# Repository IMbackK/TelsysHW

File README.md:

# Telsys Hardware

Telsys is a small integrated wireless bluetooth low energy measurement amplifier and digitizer. Its primary intention is the use with strain gauges in sensor integrated structures. Sutch as the strain reporting pipe seen below. The firmware for the nrf52 used in this design can be found here: https://github.com/IMbackK/TelsysFW. A GUI client for reciveing the data as well as to examine the data can be found here: https://github.com/IMbackK/TelsysMaster

These are kicad files detailing the shematic and board design of the Telsys device.
Kicad can be found here: https://www.kicad.org/

License: gpl-3.0 only, see license/GPL.txt

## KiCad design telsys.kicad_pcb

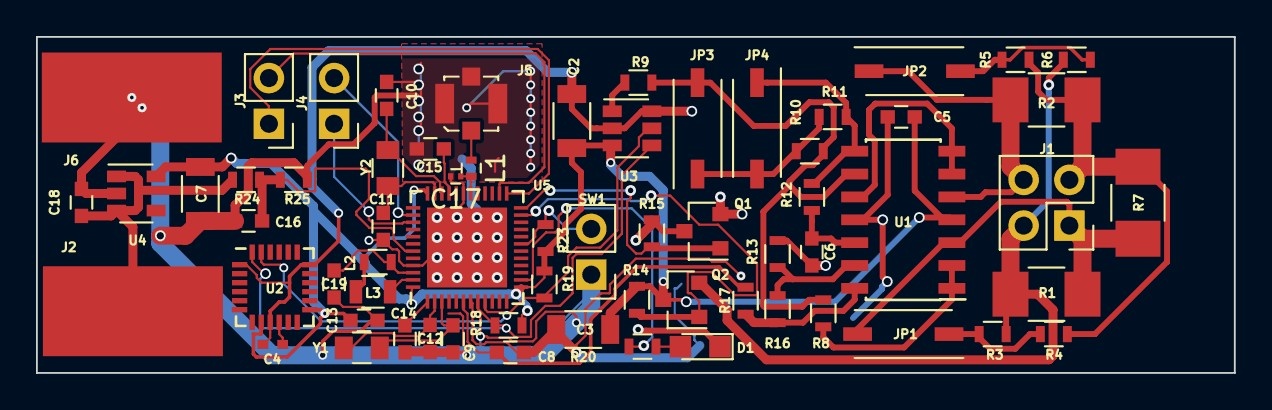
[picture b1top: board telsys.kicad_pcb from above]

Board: 2 copper layers, 66.5 x 18.7 mm, 65 parts (0 on the bottom side), 43 nets.

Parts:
C2, C3: 10nF; C_1206
C4: 0.47uF; C_0402_NoSilk
C5, C6, C8, C13, C18, C19: 1uF; C_0603
C7: 10uF; C_1206
C9, C10, C11, C12: 12pF; C_0603
C14: 100nF; C_0603
C15: 100pF; C_0603
C16: 1uf; C_0603
C17: 0.8pF; C_0201
D1: LED_RED; LED_0805
J1: Conn_02x02_Odd_Even; Pin_Header_Straight_2x02_Pitch2.54mm
J2: INPUTV; SolderWirePad_single_SMD_5x10mm
J3: PRGM; Pin_Header_Straight_1x02_Pitch2.54mm
J4: UART; Pin_Header_Straight_1x02_Pitch2.54mm
J5: Conn_Coaxial; Molex_Microcoaxial_RF
J6: INPUTGND; SolderWirePad_single_SMD_5x10mm
JP1, JP2: Jumper_NO_Small; SW_DIP_x1_W5.08mm_Slide_Copal_CHS-A
JP3, JP4: JPC; SW_DIP_x1_W5.08mm_Slide_Copal_CHS-A
L1: 3.9nH; R_0402
L2: 13nH; R_0603
L3: 10uH; R_0805
Q1: Q_NMOS_GSD; SOT-23
Q2: Q_PMOS_GSD; SOT-23
R1, R2, R7: R; R_1210_HandSoldering
R3, R4, R5, R6, R14, R15: 100K; R_0603
R8: 560R; R_0603
R9: 68K; R_0603
R10: 150K; R_0603
R11: 300K; R_0603
R12, R17: 5.6K; R_0603
R13, R16, R23: 10K; R_0603
R18, R19: 1K; R_0603
R20: 6.8k; R_0603
R24, R25: 10M; R_0603
SW1: SW_Push; Pin_Header_Straight_1x02_Pitch2.54mm
U1: LM324A; SOIC-14_3.9x8.7mm_Pitch1.27mm
U2: ICM20689; QFN-24_4x4mm_Pitch0.5mm
U3: MCP4725; SOT-23-6
U4: TLV70032_SOT23-5; SOT-23-5
U5: nrf52832-qfax; UQFN-48-1EP_6x6mm_Pitch0.4mm
Y1: 32.768KHz; C_0805
Y2: 32MHz; C_0805

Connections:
NRFGND: C7.2, C9.2, C10.2, C11.2, C12.2, C13.1, C14.1, C15.1, C16.2, C17.2, C18.2, C19.2, D1.1, J5.2, J6.1, Q1.3, R15.1, R25.1, SW1.1, U4.2, U5.31, U5.45, U5.49
unnamed: C4.1, U2.10
unnamed: C6.2, R12.2, U1.12
unnamed: C8.2, R17.2, U5.6
unnamed: C9.1, U5.3, Y1.2
unnamed: C10.1, U5.34, Y2.1
unnamed: C11.1, U5.35, Y2.2
unnamed: C12.1, U5.2, Y1.1
unnamed: C14.2, U5.1
unnamed: C15.2, U5.33
unnamed: C16.1, R24.1, R25.2, U5.43
unnamed: C17.1, L1.2, U5.30
unnamed: C18.1, J2.1, R24.2, U4.1, U4.3
unnamed: C19.1, L2.1, U5.46
unnamed: D1.2, R20.1
unnamed: J1.1, JP1.2, R1.2, R7.1, U1.3
unnamed: J1.4, JP2.1, R2.1, U1.5
unnamed: J3.1, U5.25
unnamed: J3.2, U5.26
unnamed: J4.1, U5.39
unnamed: J4.2, U5.38
unnamed: J5.1, L1.1
unnamed: JP1.1, R3.1, R4.2
unnamed: JP2.2, R5.2, R6.1
unnamed: JP3.1, JP4.2, R10.1, R11.2
unnamed: JP3.2, R8.2, R9.1, R10.2, U1.9
unnamed: JP4.1, R11.1, R12.1, U1.8
unnamed: L2.2, L3.1
unnamed: L3.2, U5.47
unnamed: Q1.1, R15.2, U5.24
unnamed: Q2.1, R14.2, U5.23
unnamed: R8.1, U1.1, U1.2
unnamed: R9.2, U3.1
unnamed: R13.2, R16.1, U1.13
unnamed: R16.2, R17.1, U1.14
unnamed: R20.2, U5.14
unnamed: R23.2, SW1.2, U5.19
unnamed: U1.6, U1.7, U1.10
SCL: R19.2, U2.23, U3.5, U5.9
SDA: R18.2, U2.24, U3.4, U5.8
VCC: C2.1, C3.1, C5.1, C7.1, C13.2, Q2.3, R14.1, R18.1, R19.1, R23.1, U1.4, U2.8, U2.13, U3.3, U4.5, U5.13, U5.36, U5.48
VGND: C2.2, C3.2, C4.2, C5.2, C6.1, C8.1, J1.3, Q1.2, R2.2, R4.1, R5.1, R7.2, R13.1, U1.11, U2.9, U2.18, U3.2, U3.6, U5.7
VSG: J1.2, Q2.2, R1.1, R3.2, R6.2

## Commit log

2021-11-03 inital commit
2021-11-03 add some documentation
